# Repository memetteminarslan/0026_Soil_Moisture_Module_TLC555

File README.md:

# 0026_Soil_Moisture_Module_TLC555

You are seeing a large number of widely used soil mouisture modules in electronic development kits. More information coming soon...

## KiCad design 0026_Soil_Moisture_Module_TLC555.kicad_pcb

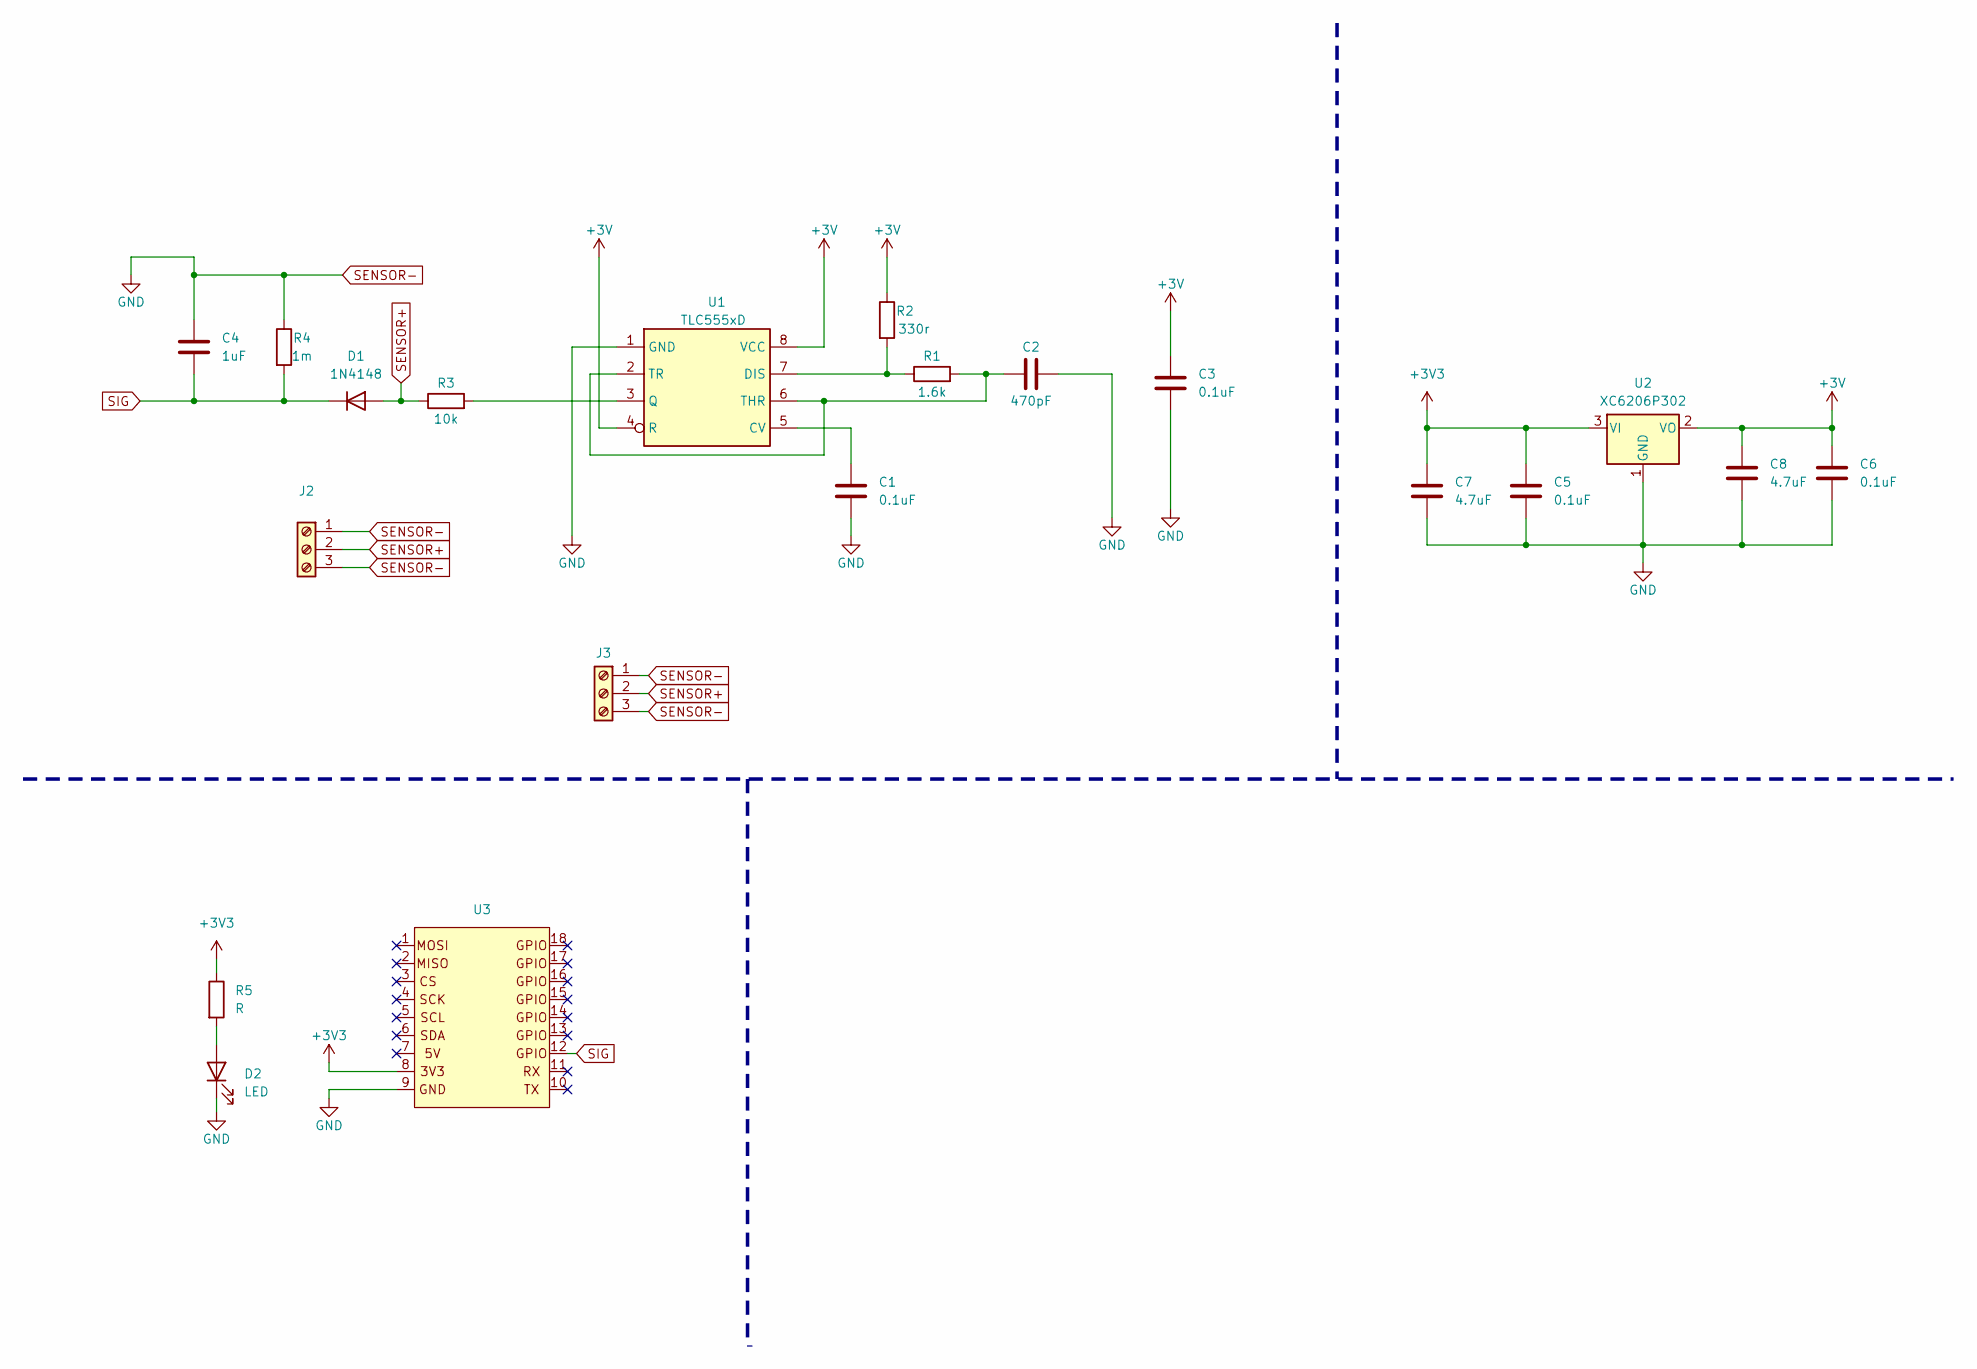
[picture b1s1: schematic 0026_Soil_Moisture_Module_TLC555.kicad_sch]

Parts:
C1, C3, C5, C6: 0.1uF; C_0603_1608Metric
C2: 470pF; C_0603_1608Metric
C4: 1uF; C_0603_1608Metric
C7, C8: 4.7uF; C_0603_1608Metric
D1: 1N4148; D_0805_2012Metric
D2: LED; LED_0603_1608Metric
J2, J3: Screw_Terminal_01x03; TerminalBlock_4Ucon_1x03_P3.50mm_Horizontal
R1: 1.6k; R_0603_1608Metric
R2: 330r; R_0603_1608Metric
R3: 10k; R_0603_1608Metric
R4: 1m; R_0603_1608Metric
R5: R; R_0603_1608Metric
U1: TLC555xD; SOIC-8_3.9x4.9mm_P1.27mm
U2: XC6206P302; SOT-23-3
U3: pin_header

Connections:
+3V3: C5.1, C7.1, R5.1, U2.3 (VI), U3.8
unnamed: D2.2 (A), R5.2
unnamed: C1.1, U1.5 (CV)
unnamed: R1.1, R2.2, U1.7 (DIS)
unnamed: R3.2, U1.3 (Q)
unnamed: C2.1, R1.2, U1.2 (TR), U1.6 (THR)
SENSOR+: D1.2 (A), J2.2, J3.2, R3.1
SENSOR-: C1.2, C2.2, C3.1, C4.1, C5.2, C6.2, C7.2, C8.2, D2.1 (K), J2.1, J2.3, J3.1, J3.3, R4.1, U1.1 (GND), U2.1 (GND), U3.9
SIG: C4.2, D1.1 (K), R4.2, U3.12
VCC: C3.2, C6.1, C8.1, R2.1, U1.4 (R), U1.8 (VCC), U2.2 (VO)

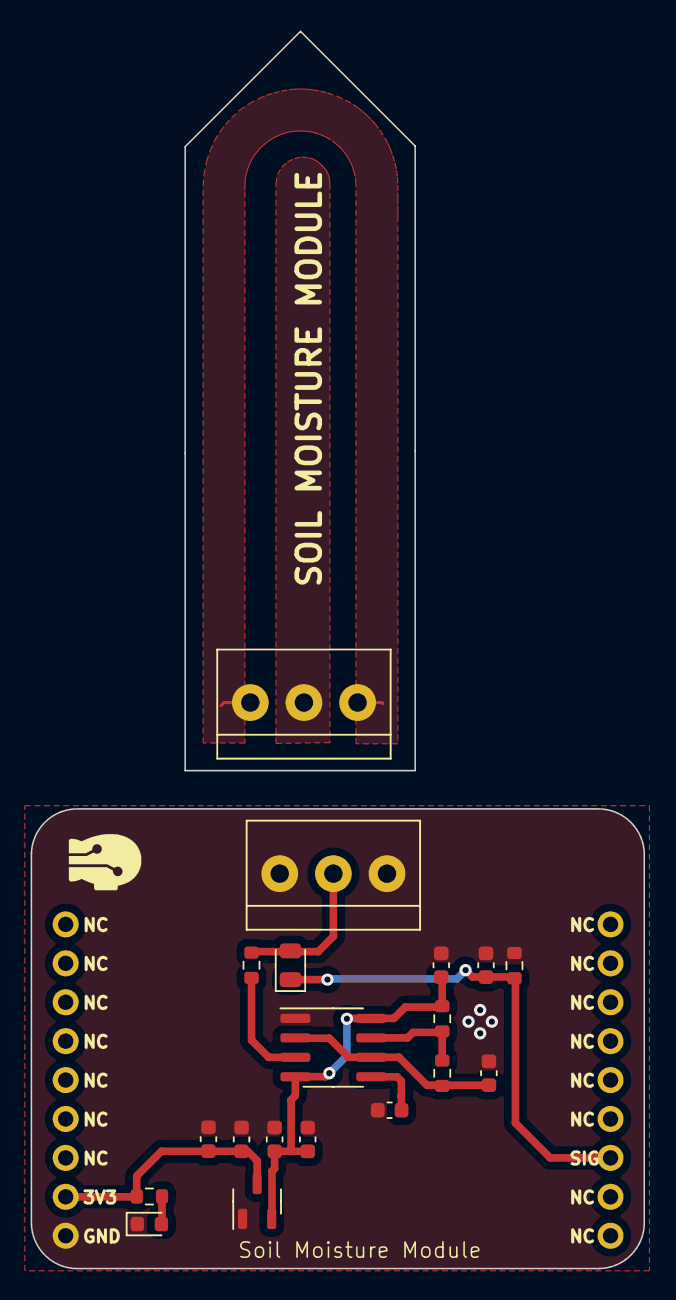
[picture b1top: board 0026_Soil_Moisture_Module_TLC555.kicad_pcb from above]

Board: 2 copper layers, 40.0 x 80.7 mm, 20 parts (0 on the bottom side), 10 nets.
